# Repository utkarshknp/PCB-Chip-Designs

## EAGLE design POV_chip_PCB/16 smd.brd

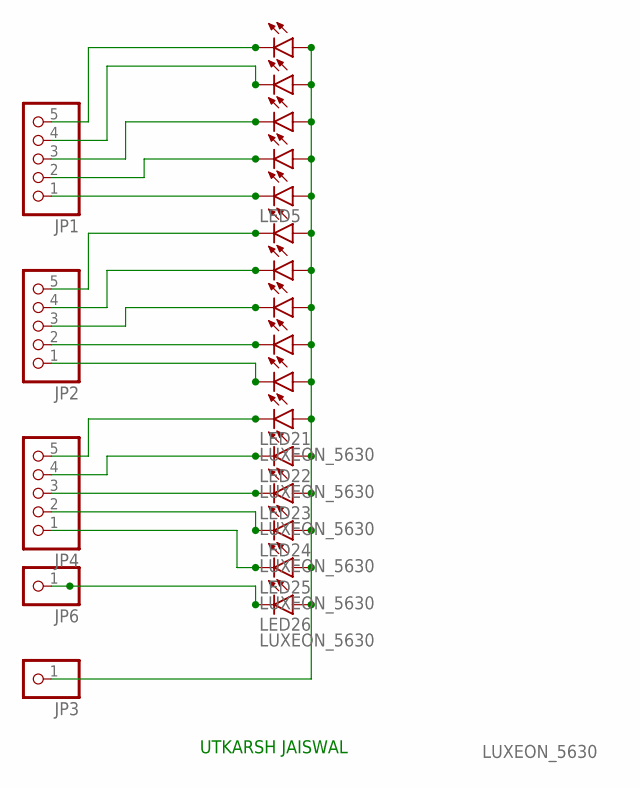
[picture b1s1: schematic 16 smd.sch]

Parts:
JP1, JP2, JP4: PINHD-1X5; 1X05
JP3, JP6: PINHD-1X1; 1X01
LED1, LED2, LED3, LED4, LED5, LED6, LED7, LED8, LED9, LED10, LED21, LED22, LED23, LED24, LED25, LED26: LUXEON_5630

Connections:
unnamed: JP1.5, LED1.1@1 (C), LED1.1@2 (C)
unnamed: JP1.4, LED2.1@1 (C), LED2.1@2 (C)
unnamed: JP1.3, LED3.1@1 (C), LED3.1@2 (C)
unnamed: JP1.2, LED4.1@1 (C), LED4.1@2 (C)
unnamed: JP1.1, LED5.1@1 (C), LED5.1@2 (C)
unnamed: JP2.5, LED6.1@1 (C), LED6.1@2 (C)
unnamed: JP2.4, LED7.1@1 (C), LED7.1@2 (C)
unnamed: JP2.3, LED8.1@1 (C), LED8.1@2 (C)
unnamed: JP2.2, LED9.1@1 (C), LED9.1@2 (C)
unnamed: JP2.1, LED10.1@1 (C), LED10.1@2 (C)
unnamed: JP4.5, LED21.1@1 (C), LED21.1@2 (C)
unnamed: JP4.4, LED22.1@1 (C), LED22.1@2 (C)
unnamed: JP4.3, LED23.1@1 (C), LED23.1@2 (C)
unnamed: JP4.2, LED24.1@1 (C), LED24.1@2 (C)
unnamed: JP4.1, LED25.1@1 (C), LED25.1@2 (C)
unnamed: JP6.1, LED26.1@1 (C), LED26.1@2 (C)
unnamed: JP3.1, LED1.2 (A), LED2.2 (A), LED3.2 (A), LED4.2 (A), LED5.2 (A), LED6.2 (A), LED7.2 (A), LED8.2 (A), LED9.2 (A), LED10.2 (A), LED21.2 (A), LED22.2 (A), LED23.2 (A), LED24.2 (A), LED25.2 (A), LED26.2 (A)

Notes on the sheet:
UTKARSH JAISWAL

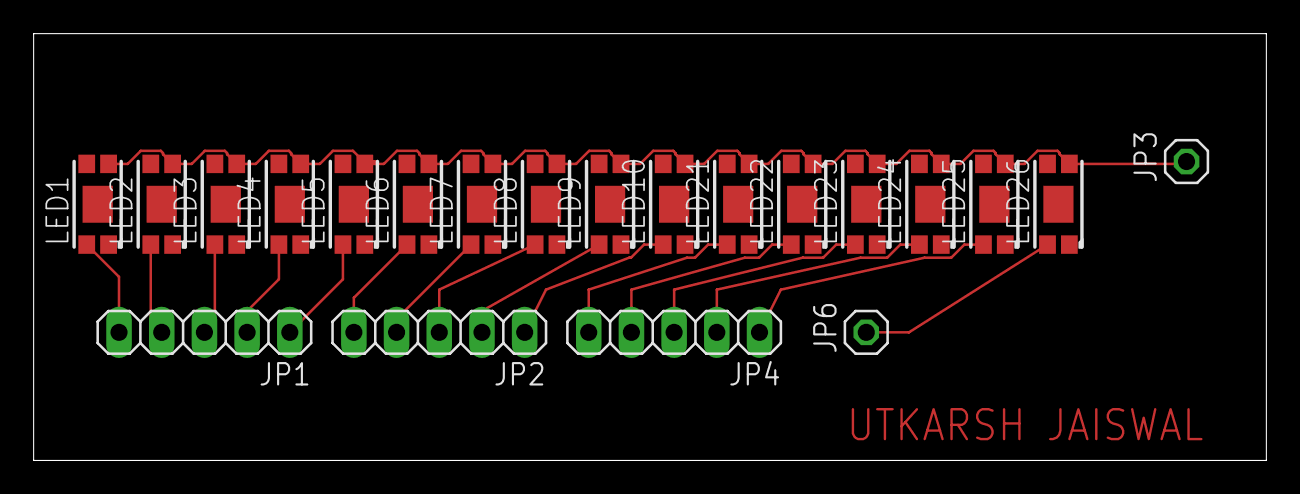
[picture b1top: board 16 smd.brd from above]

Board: 2 copper layers, 73.3 x 25.4 mm, 21 parts (0 on the bottom side), 17 nets.

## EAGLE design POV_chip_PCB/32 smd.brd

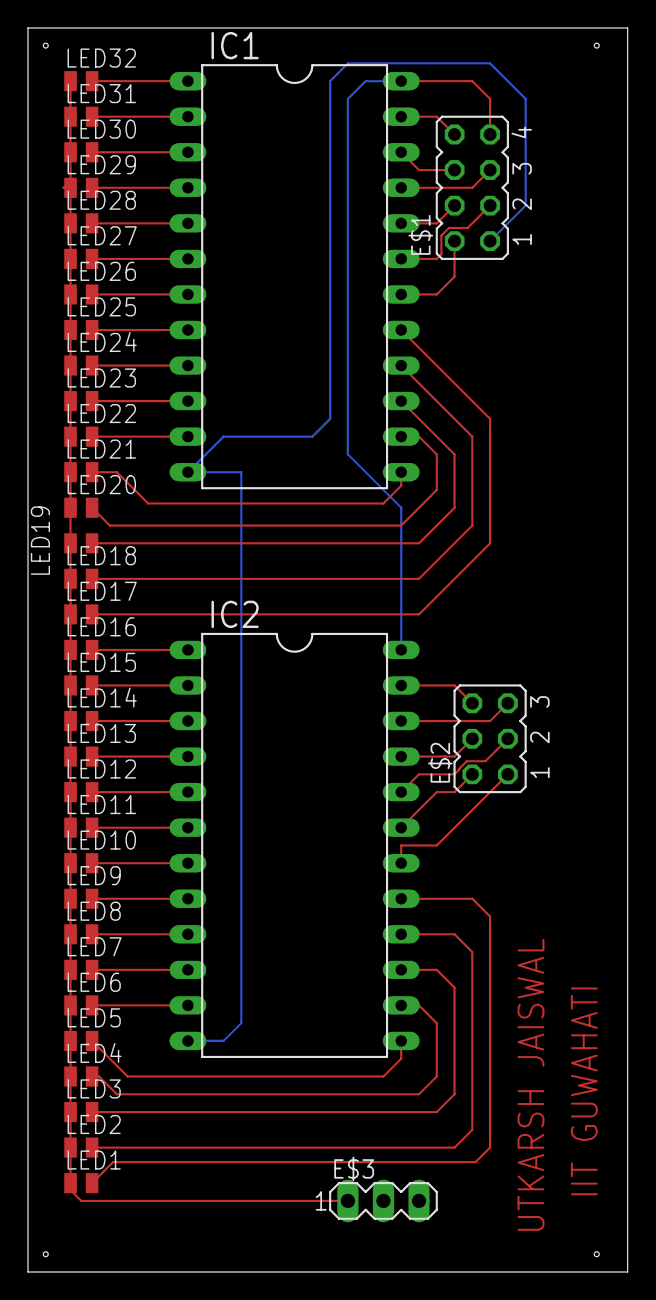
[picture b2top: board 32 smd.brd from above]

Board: 2 copper layers, 42.9 x 88.9 mm, 37 parts (0 on the bottom side), 47 nets.

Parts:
E$1: JP4Q
E$2: JP3Q
E$3: MA03-1
IC1, IC2: 74154N; DIL24-6
LED1, LED2, LED3, LED4, LED5, LED6, LED7, LED8, LED9, LED10, LED11, LED12, LED13, LED14, LED15, LED16, LED17, LED18, LED19, LED20, LED21, LED22, LED23, LED24, LED25, LED26, LED27, LED28, LED29, LED30, LED31, LED32: GM1BW76340A; GM1BW78140A

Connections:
GND: E$1.1, IC1.12, IC2.12
unnamed: E$3.1, LED1.C, LED2.C, LED3.C, LED4.C, LED5.C, LED6.C, LED7.C, LED8.C, LED9.C, LED10.C, LED11.C, LED12.C, LED13.C, LED14.C, LED15.C, LED16.C, LED17.C, LED18.C, LED19.C, LED20.C, LED21.C, LED22.C, LED23.C, LED24.C, LED25.C, LED26.C, LED27.C, LED28.C, LED29.C, LED30.C, LED31.C, LED32.C
unnamed: IC1.1, LED32.A
unnamed: IC1.2, LED31.A
unnamed: IC1.3, LED30.A
unnamed: IC1.4, LED29.A
unnamed: IC1.5, LED28.A
unnamed: IC1.6, LED27.A
unnamed: IC1.7, LED26.A
unnamed: IC1.8, LED25.A
unnamed: IC1.9, LED24.A
unnamed: IC1.10, LED23.A
unnamed: IC1.11, LED22.A
unnamed: IC1.13, LED21.A
unnamed: IC1.14, LED20.A
unnamed: IC1.15, LED19.A
unnamed: IC1.16, LED18.A
unnamed: IC1.17, LED17.A
unnamed: IC2.1, LED16.A
unnamed: IC2.2, LED15.A
unnamed: IC2.3, LED14.A
unnamed: IC2.4, LED13.A
unnamed: IC2.5, LED12.A
unnamed: IC2.6, LED11.A
unnamed: IC2.7, LED10.A
unnamed: IC2.8, LED9.A
unnamed: IC2.9, LED8.A
unnamed: IC2.10, LED7.A
unnamed: IC2.11, LED6.A
unnamed: IC2.13, LED5.A
unnamed: IC2.14, LED4.A
unnamed: IC2.15, LED3.A
unnamed: IC2.16, LED2.A
unnamed: IC2.17, LED1.A
S$1: E$2.6, IC2.23
S$2: E$2.5, IC2.22
S$3: E$2.4, IC2.21
S$4: E$2.3, IC2.20
S$5: E$2.2, IC2.19
S$6: E$2.1, IC2.18
S$7: E$1.8, IC1.23
S$8: E$1.6, IC1.22
S$9: E$1.5, IC1.21
S$10: E$1.4, IC1.20
S$11: E$1.3, IC1.19
S$12: E$1.2, IC1.18
VCC: E$1.7, IC1.24, IC2.24

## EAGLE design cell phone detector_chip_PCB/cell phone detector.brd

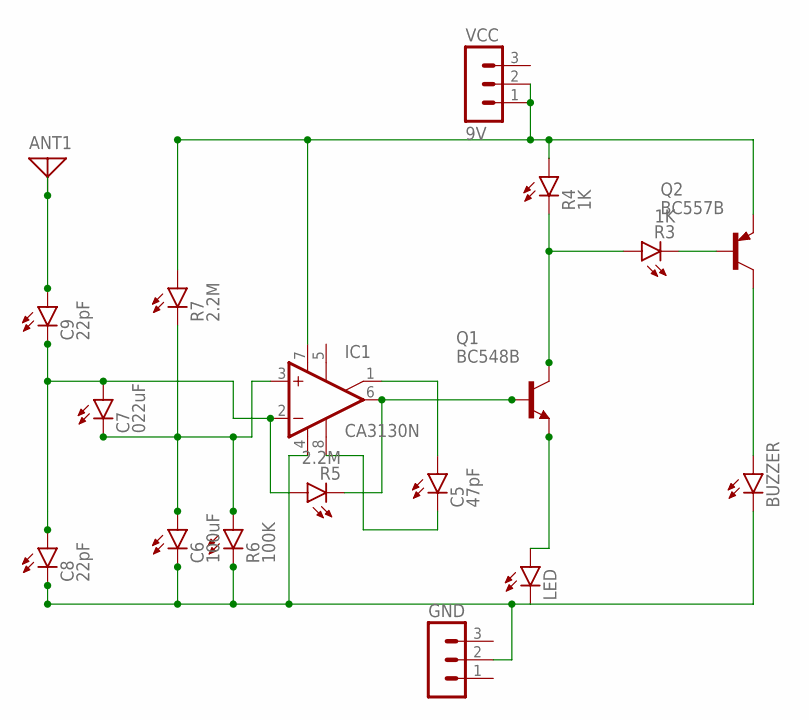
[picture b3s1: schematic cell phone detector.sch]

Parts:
ANT1: ANTENNA; PAD-01
BUZZER: LED5MM
C5: 47pF; LED5MM
C6: 100uF; LED5MM
C7: 022uF; LED5MM
C8, C9: 22pF; LED5MM
GND: MA03-1
IC1: CA3130N; DIL08
LED: LED5MM
Q1: BC548B; TO92-EBC
Q2: BC557B; TO92-EBC
R3, R4: 1K; LED5MM
R5, R7: 2.2M; LED5MM
R6: 100K; LED5MM
VCC: 9V; MA03-1

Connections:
unnamed: Q2.B, R3.K (C)
unnamed: ANT1.1, C9.A
unnamed: IC1.7 (V+), Q2.E, R4.A, R7.A, VCC.1, VCC.2
unnamed: LED.A, Q1.E
unnamed: Q1.C, R3.A, R4.K (C)
unnamed: C6.A, C7.K (C), IC1.3 (+IN), R6.A, R7.K (C)
unnamed: IC1.6 (OUT), Q1.B, R5.K (C)
unnamed: BUZZER.A, Q2.C
unnamed: C7.A, C8.A, C9.K (C), IC1.2 (-IN), R5.A
unnamed: BUZZER.K (C), C6.K (C), C8.K (C), GND.2, IC1.4 (V-), LED.K (C), R6.K (C)
unnamed: C5.A, IC1.1 (ON/CMP)
unnamed: C5.K (C), IC1.8 (CMP)

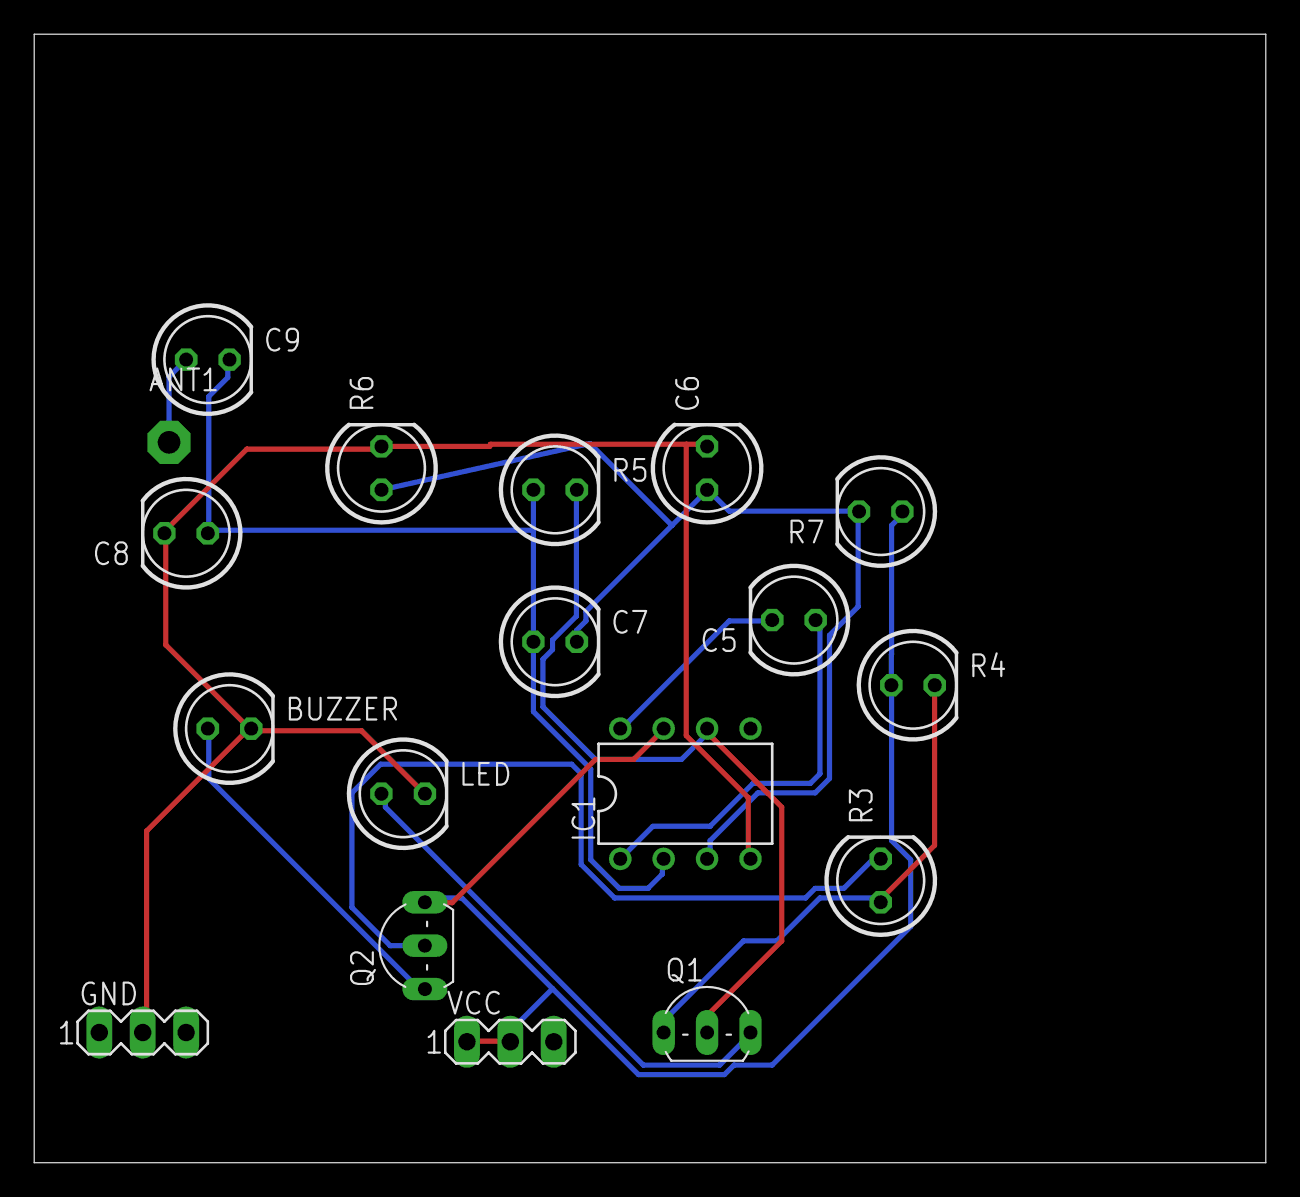
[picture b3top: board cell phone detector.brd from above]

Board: 2 copper layers, 72.1 x 66.0 mm, 18 parts (0 on the bottom side), 12 nets.

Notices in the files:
parts and their libraries:
led: Lumileds 5630 Datasheet DS201 20130228 ©2013 Philips Lumileds Lighting Company.
